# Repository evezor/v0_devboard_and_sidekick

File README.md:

# Devboard and Sidekick
*please note this board has been deprecated.

An edge board that is meant to be a development board that breaks out all the pins. And a second board that is meant to assist, that has a small prototyping area.  

source files can be found here: https://github.com/evezor/v0_devboard_and_sidekick

This board uses the Evezor Stamp STMF405 MCU

source: https://github.com/evezor/Evezor-Stamp-STMF405

Evezor® and all associated marks, logos, and designs are registered trademarks and protected by copyright. Unauthorized use or reproduction of these trademarks and copyrighted materials is strictly prohibited.

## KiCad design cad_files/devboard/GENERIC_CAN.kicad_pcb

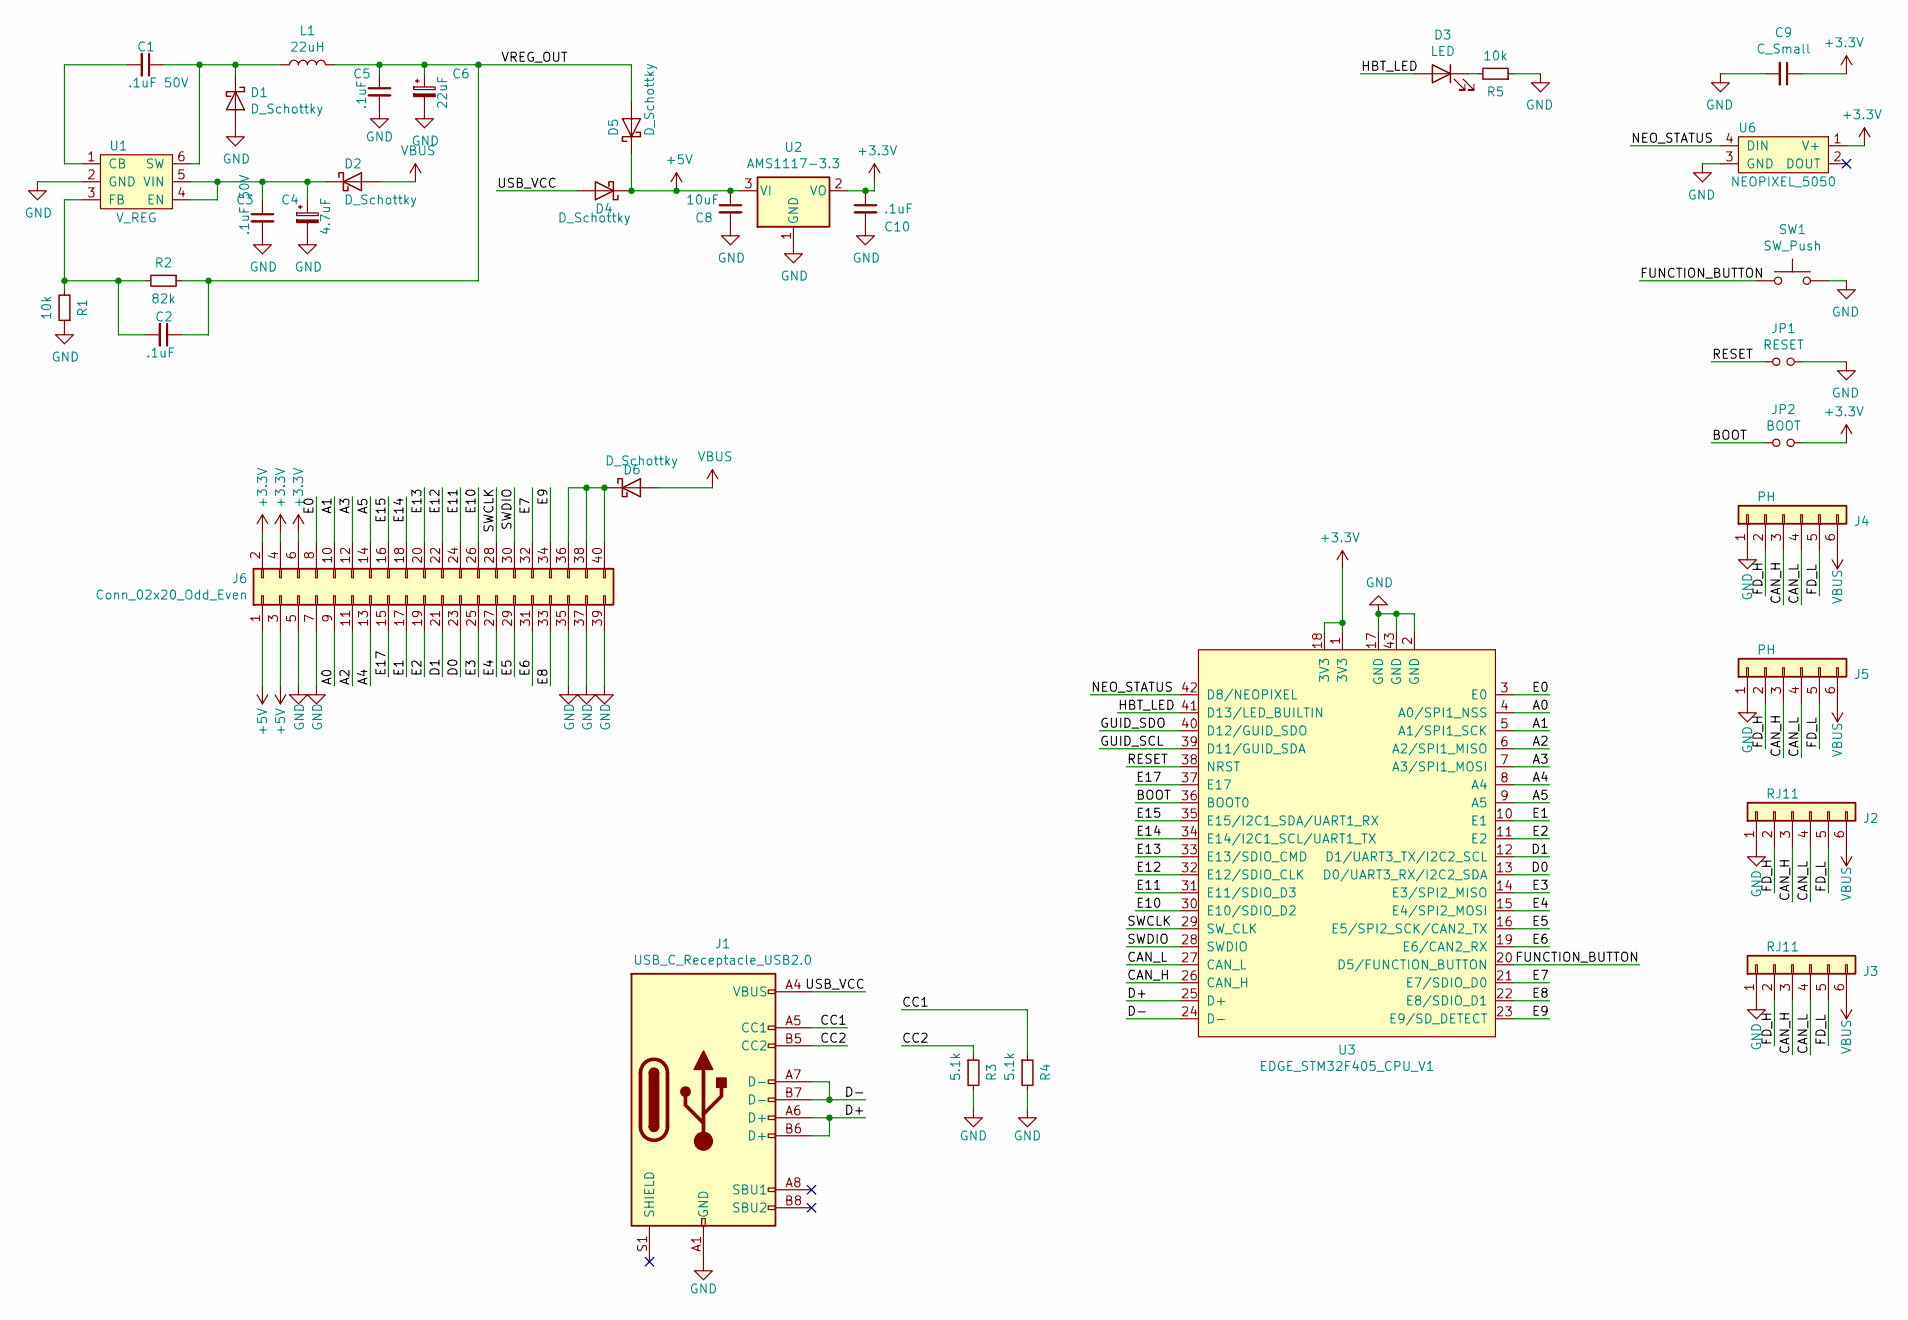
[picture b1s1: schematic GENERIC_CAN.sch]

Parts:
C1, C3: .1uF 50V; C_0603_1608Metric
C2, C5, C10: .1uF; C_0603_1608Metric
C4: 4.7uF; C_0805_2012Metric
C6: 22uF; C_0805_2012Metric
C8: 10uF; C_0805_2012Metric
C9: C_Small; C_0603_1608Metric
D1, D2, D4, D5, D6: D_Schottky; D_SMA
D3: LED; LED_0603_1608Metric
J1: USB_C_Receptacle_USB2.0; USB_C_Receptacle_HRO_TYPE-C-31-M-12
J2, J3: RJ11; RJ11_C189747_Horizontal
J4, J5: PH; JST_PH_B6B-PH-K_1x06_P2.00mm_Vertical
J6: Conn_02x20_Odd_Even; IDC-Header_2x20_P2.54mm_Vertical
JP1: RESET; SHORT_PAD
JP2: BOOT; SHORT_PAD
L1: 22uH; INDUCTOR_7.5X6.6_GCDA0630-220MC
R1, R5: 10k; R_0603_1608Metric
R2: 82k; R_0603_1608Metric
R3, R4: 5.1k; R_0603_1608Metric
SW1: SW_Push; SWITCH_2x3_SMD_TACTILE_GREEN
U1: V_REG; SOT-23-6
U2: AMS1117-3.3; SOT-223-3_TabPin2
U3: EDGE_STM32F405_CPU_V1; EDGE_STAMP
U6: NEOPIXEL_5050

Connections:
+3V3: C9.1, C10.1, J6.2, J6.4, J6.6, JP2.2, U2.2 (VO), U3.1 (3V3), U3.18 (3V3), U6.1 (V+); also elsewhere on the board
+5V: C8.1, D4.1 (K), D5.1 (K), J6.1, J6.3, U2.3 (VI)
/A0: J6.9, U3.4 (A0/SPI1_NSS)
/A1: J6.10, U3.5 (A1/SPI1_SCK)
/A2: J6.11, U3.6 (A2/SPI1_MISO)
/A3: J6.12, U3.7 (A3/SPI1_MOSI)
/A4: J6.13, U3.8 (A4)
/A5: J6.14, U3.9 (A5)
/BOOT: JP2.1, U3.36 (BOOT0)
/CAN_H: J2.3, J3.3, J4.3, J5.3, U3.26 (CAN_H)
/CAN_L: J2.4, J3.4, J4.4, J5.4, U3.27 (CAN_L)
/CC1: J1.A5 (CC1), R4.1
/CC2: J1.B5 (CC2), R3.1
/D0: J6.23, U3.13 (D0/UART3_RX/I2C2_SDA)
/D1: J6.21, U3.12 (D1/UART3_TX/I2C2_SCL)
/D+: J1.A6 (D+), J1.B6 (D+), U3.25 (D+)
/D-: J1.A7 (D-), J1.B7 (D-), U3.24 (D-)
/E0: J6.8, U3.3 (E0)
/E1: J6.17, U3.10 (E1)
/E2: J6.19, U3.11 (E2)
/E3: J6.25, U3.14 (E3/SPI2_MISO)
/E4: J6.27, U3.15 (E4/SPI2_MOSI)
/E5: J6.29, U3.16 (E5/SPI2_SCK/CAN2_TX)
/E6: J6.31, U3.19 (E6/CAN2_RX)
/E7: J6.32, U3.21 (E7/SDIO_D0)
/E8: J6.33, U3.22 (E8/SDIO_D1)
/E9: J6.34, U3.23 (E9/SD_DETECT)
/E10: J6.26, U3.30 (E10/SDIO_D2)
/E11: J6.24, U3.31 (E11/SDIO_D3)
/E12: J6.22, U3.32 (E12/SDIO_CLK)
/E13: J6.20, U3.33 (E13/SDIO_CMD)
/E14: J6.18, U3.34 (E14/I2C1_SCL/UART1_TX)
/E15: J6.16, U3.35 (E15/I2C1_SDA/UART1_RX)
/E17: J6.15, U3.37 (E17)
/FD_H: J2.2, J3.2, J4.2, J5.2
/FD_L: J2.5, J3.5, J4.5, J5.5
/FUNCTION_BUTTON: SW1.1, U3.20 (D5/FUNCTION_BUTTON)
/GUID_SCL: U3.39 (D11/GUID_SDA); also elsewhere on the board
/GUID_SDO: U3.40 (D12/GUID_SDO); also elsewhere on the board
/HBT_LED: D3.2 (A), U3.41 (D13/LED_BUILTIN)
/NEO_STATUS: U3.42 (D8/NEOPIXEL), U6.4 (DIN)
/RESET: JP1.1, U3.38 (NRST)
/SWCLK: J6.28, U3.29 (SW_CLK)
/SWDIO: J6.30, U3.28 (SWDIO)
/USB_VCC: D4.2 (A), J1.A4 (VBUS), J1.A9 (VBUS), J1.B4 (VBUS), J1.B9 (VBUS)
/VREG_OUT: C2.1, C5.1, C6.1, D5.2 (A), L1.2, R2.1
GND: C3.2, C4.2, C5.2, C6.2, C8.2, C9.2, C10.2, D1.2 (A), J1.A1 (GND), J1.A12 (GND), J1.B1 (GND), J1.B12 (GND), J2.1, J3.1, J4.1, J5.1, J6.5, J6.7, J6.35, J6.37, J6.39, JP1.2, R1.1, R3.2, R4.2, R5.1, SW1.2, U1.2 (GND), U2.1 (GND), U3.2 (GND), U3.17 (GND), U3.43 (GND), U6.3 (GND); also elsewhere on the board
unnamed: C1.1, D1.1 (K), L1.1, U1.6 (SW)
unnamed: C1.2, U1.1 (CB)
unnamed: C2.2, R1.2, R2.2, U1.3 (FB)
unnamed: C3.1, C4.1, D2.1 (K), U1.4 (EN), U1.5 (VIN)
unnamed: D3.1 (K), R5.2
unnamed: D6.1 (K), J6.36, J6.38, J6.40
VBUS: D2.2 (A), D6.2 (A), J2.6, J3.6, J4.6, J5.6

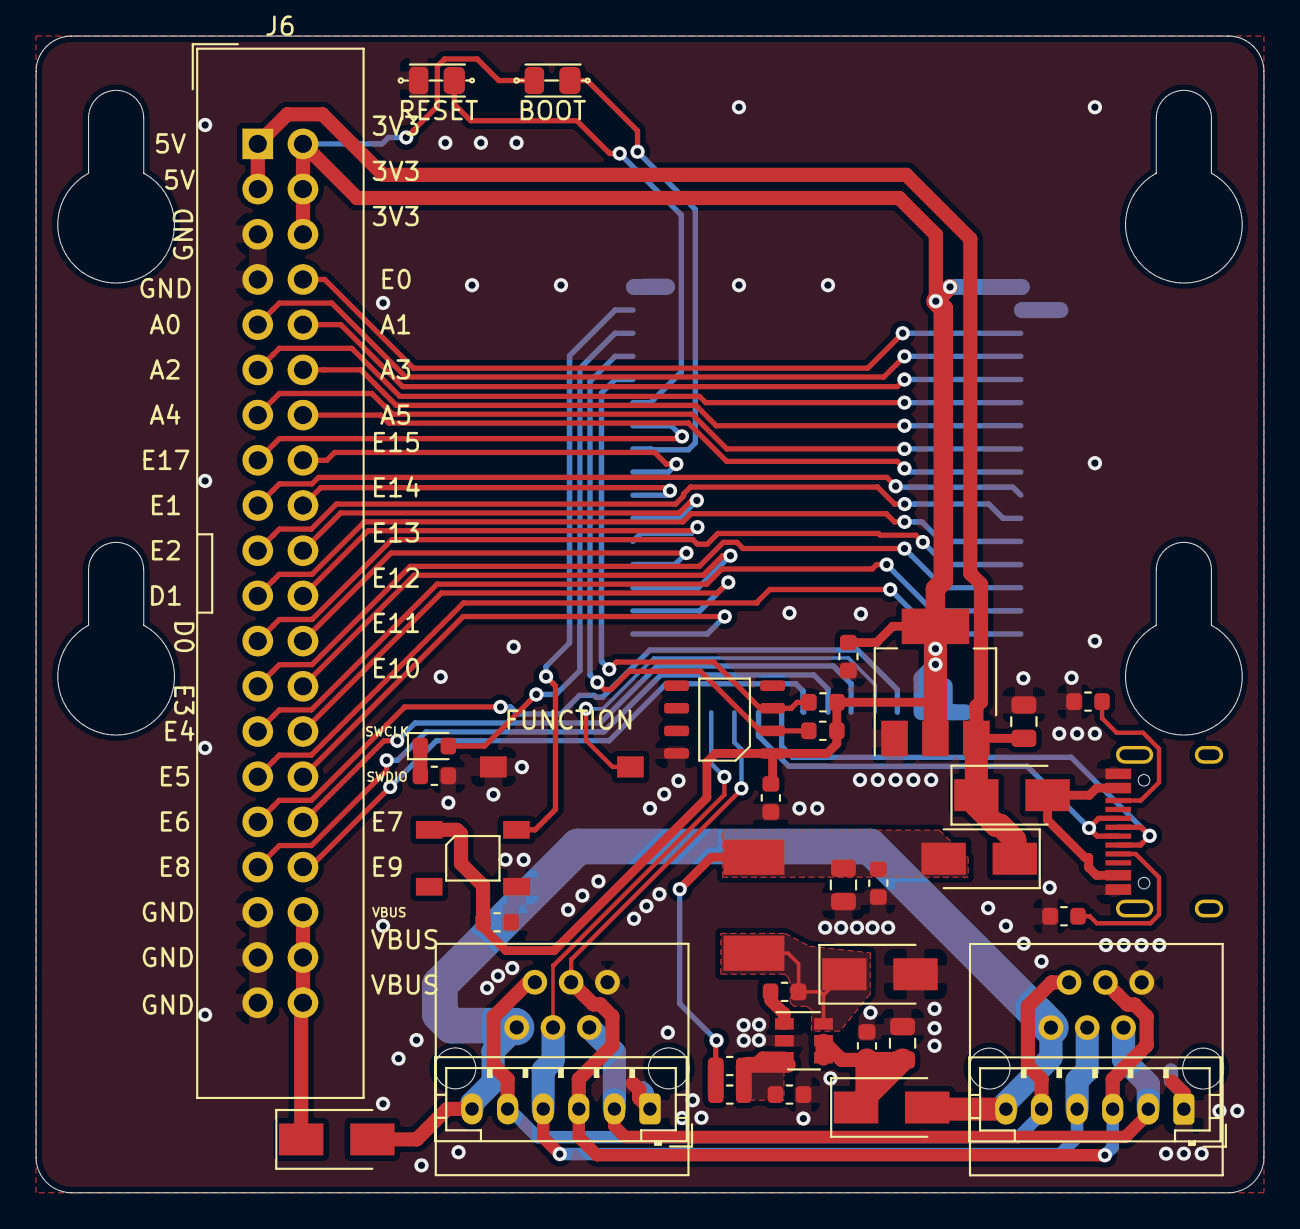
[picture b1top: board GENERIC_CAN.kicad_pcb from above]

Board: 2 copper layers, 69.0 x 65.0 mm, 38 parts (1 on the bottom side), 54 nets.

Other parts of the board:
C7: .1uF; C_0603_1608Metric
R6, R7: R_Small; R_0603_1608Metric
U4: MICOCONTROLLER_GUID_SOP-8; GUID_PS150C

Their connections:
+3V3: C7.1, R6.2, R7.2, U4.1; also elsewhere on the board
/GUID_SCL: R7.1, U4.3; also elsewhere on the board
/GUID_SDO: R6.1, U4.2; also elsewhere on the board
GND: C7.2, U4.8; also elsewhere on the board

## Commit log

2023-09-11 init
